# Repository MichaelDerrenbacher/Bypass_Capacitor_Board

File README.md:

# Bypass_Capacitor_Board
Board to visualize the effects of bypass capacitors on an IC with a fast slew rate output

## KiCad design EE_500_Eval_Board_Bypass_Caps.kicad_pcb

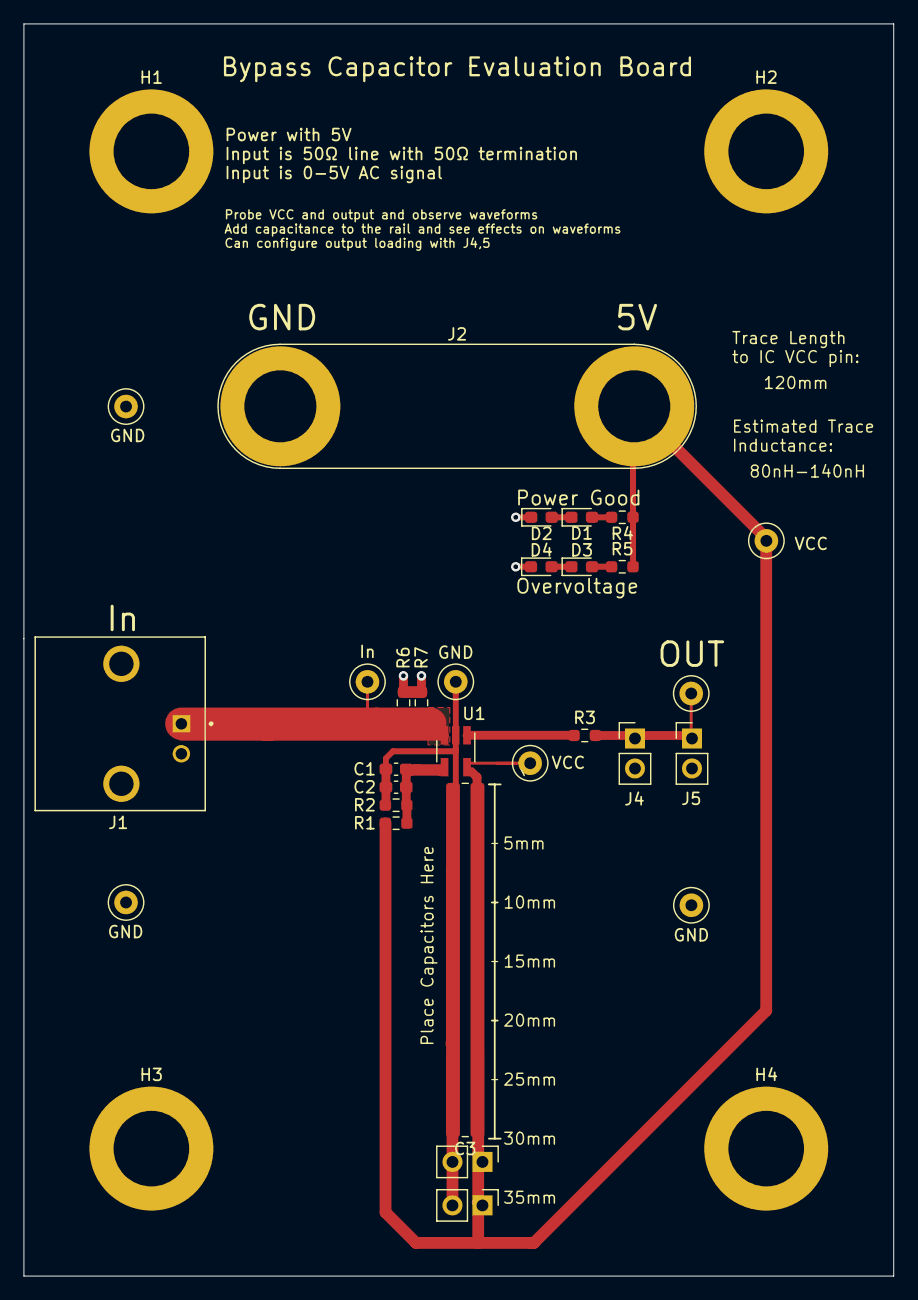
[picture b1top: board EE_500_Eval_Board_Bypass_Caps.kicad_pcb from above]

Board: 2 copper layers, 73.7 x 106.0 mm, 33 parts (0 on the bottom side), 11 nets.

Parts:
C1: 100n; C_0603_1608Metric_Pad1.08x0.95mm_HandSolder
C2: 1u; C_0603_1608Metric_Pad1.08x0.95mm_HandSolder
C3: C; Test_strip
D1, D2, D3, D4: LED; LED_0603_1608Metric_Pad1.05x0.95mm_HandSolder
GND: TestPoint; TestPoint_Loop_D2.50mm_Drill1.0mm
GND#2, GND#3, GND#4: TestPoint; TestPoint_Loop_D2.50mm_Drill1.0mm
H1, H2, H3, H4: MountingHole; MountingHole_6.4mm_M6_ISO7380_Pad
In: TestPoint; TestPoint_Loop_D2.50mm_Drill1.0mm
J1: 1-1634612-0; TE_1-1634612-0
J2: Conn_01x02; Banana_Jack_2Pin
J3, J4, J5, J6: Conn_01x02_Female; PinHeader_1x02_P2.54mm_Vertical
OUT: TestPoint; TestPoint_Loop_D2.50mm_Drill1.0mm
R1, R2: 10k; R_0603_1608Metric_Pad0.98x0.95mm_HandSolder
R3: 0; R_0603_1608Metric_Pad0.98x0.95mm_HandSolder
R4, R6, R7: 100; R_0603_1608Metric_Pad0.98x0.95mm_HandSolder
R5: 330; R_0603_1608Metric_Pad0.98x0.95mm_HandSolder
U1: TLV3201; SOT-23-5_HandSoldering
VCC: TestPoint; TestPoint_Loop_D2.50mm_Drill1.0mm
VCC#2: TestPoint; TestPoint_Loop_D2.50mm_Drill1.0mm

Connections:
0: C1.2, C2.2, C3.2, D2.1, D4.1, GND.1, GND#2.1, GND#3.1, GND#4.1, J1.2, J2.2, J3.2, J4.2, J5.2, J6.2, R2.2, R6.2, R7.2, U1.2
In+: In.1, J1.1, R6.1, R7.1, U1.3
In-: C1.1, C2.1, R1.2, R2.1, U1.4
unnamed: D1.1, D2.2
unnamed: D1.2, R4.2
unnamed: D3.1, D4.2
unnamed: D3.2, R5.2
unnamed: J1.S1, J1.S2
unnamed: R3.2, U1.1
Out: J4.1, J5.1, OUT.1, R3.1
VCC: C3.1, J2.1, J3.1, J6.1, R1.1, R4.1, R5.1, U1.5, VCC.1, VCC#2.1
